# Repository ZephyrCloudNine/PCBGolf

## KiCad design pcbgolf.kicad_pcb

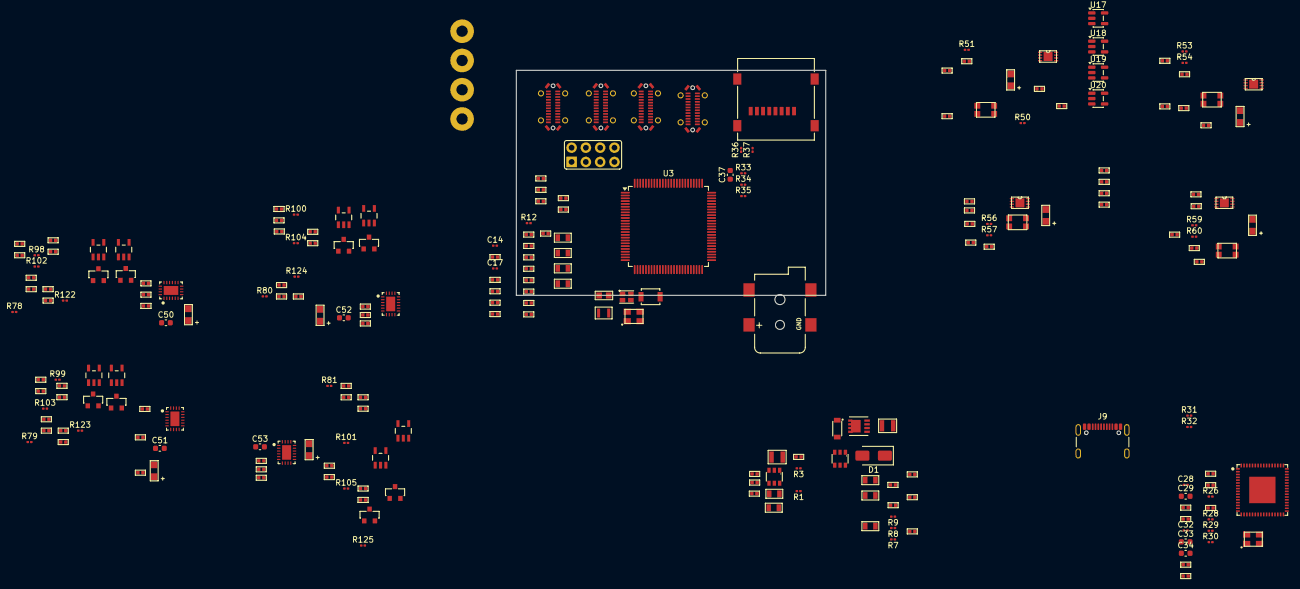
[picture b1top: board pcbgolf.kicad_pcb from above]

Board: 4 copper layers, 55.0 x 40.0 mm, 232 parts (0 on the bottom side), 184 nets, no tracks yet.

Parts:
BH1, BH2, BH3, BH4: M2_BOLT
C1, C3, C8, C12, C13, C15, C19, C20, C21: 10uF; 0805-C
C2, C4, C5, C7, C9, C11, C16, C18, C22, C23, C24, C26, C27, C30, C31, C35, C36, C38, C39, C40, C41, C42, C43, C44, C45, C46, C47, C48, C49: 100nF; 0402-C
C14, C17, C28, C32: 12pF; C_0201_0603Metric
C25: 220pF; 0402-C
C29, C33, C34, C37, C50, C51, C52, C53: 10uF; C_0603_1608Metric
D1: TVS-BI-DO214AA; D_SMA
D2: DIODEDB2W40100L; SOD-123F
J1: DCBARRELSMT; DCJACK_2MM_SMT
J2: MICRO_SD-0472192001; 0472192001
J4: CAN; 2X04
J5, J6, J7, J8: USB-C-FEMALEGCT; USB-C-FEMALE-VERT-GCT
J9: USB_C_Receptacle_USB2.0_16P; USB_C_Receptacle_GCT_USB4105-xx-A_16P_TopMnt_Horizontal
L1, L2: 3u3; L-1008
L3: L-US-L2; 0603-L
L4: 2u2; 0806
L5, L6, L7, L8: ACT1210D_CHOKE; CHOKE-3.2X2.5
LED1: CREE-RGB-CLMVC
LED2: CAN0; CHIPLED
LED3: CAN1; CHIPLED
LED4: CAN2; CHIPLED
LED5: CAN3; CHIPLED
LED6, LED7, LED8, LED9: CH1_PWR; CHIPLED
LED10, LED11, LED12, LED13, LED14, LED15, LED16, LED17: LED-CC-GREEN-RED-AM23ESG; SOT23-3
Q1: SIS427-VI; PP-1212-8
Q2, Q3, Q4, Q5, Q6, Q7, Q8, Q9: NFET-DUAL-COMMON-SOURCE-QS5K2; SOT23-5
R1, R3, R7, R8, R9, R12, R28, R29, R30, R33, R34, R35, R36, R37, R50, R51, R53, R54, R56, R57, R59, R60, R78, R79, R80, R81, R98, R99, R100, R101, R102, R103, R104, R105, R122, R123, R124, R125: 10k; R_0201_0603Metric
R2, R21, R23, R90, R92, R94, R96, R114, R116, R118, R120: 1k; 0402-R
R4: 33K3; 0402-R
R10: 52k3; 0402-R
R13, R14, R15, R16, R17, R18, R19, R20, R24, R25, R52, R55, R58, R61: 100k; 0402-R
R22, R62, R63, R64, R65: 2k7; 0402-R
R26: 1M; R_0201_0603Metric
R27: 12k; 0402-R
R31, R32: 5.1K; R_0201_0603Metric
R46, R47, R48, R49: 60; 0402-R
R66, R67, R68, R69: 28k; 0402-R
R70, R71, R72, R73: 33k; 0402-R
R74, R75, R76, R77: 3k3; 0402-R
R82, R83, R84, R85, R86, R87, R88, R89, R91, R93, R95, R97, R106, R107, R108, R109, R110, R111, R112, R113, R115, R117, R119, R121: 100; 0402-R
SW1: SW_SPST; SW_SPST_B3U-1000P
U1, U2: AP62300T; SOT23-6
U3: STM32H725ZGTx; LQFP-100_14x14mm_P0.5mm
U4: USB2517; QFN64-9X9
U5, U6, U7, U8: MCP2542FDT-E/MNY; TDFN8_2X3MC_MCH
U13, U14, U15, U16: TPS25942; WQFN20
U17, U18, U19, U20: OPA197xDBV; SOT-23-5
Y1: 25MHz; XTAL-3.2X2.5
Y2: 24MHz; XTAL-3.2X2.5

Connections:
+3V3: C7.1, C8.1, C19.1, C20.1, C23.1, C24.1, C26.1, C27.1, C30.2, C31.2, C37.1, C42.1, C43.1, C44.1, C45.1, J2.4 (VDD), L1.2, L3.1, LED1.U1 (COM+), R4.1, R28.1, R29.1, R30.1, R33.1, R34.1, R35.1, R36.1, R37.1, SW1.2 (B), U3.4 (VDD), U3.5 (VBAT), U3.11 (VDDSMPS), U3.20 (VDD), U3.30 (VDD), U3.47 (VDD), U3.59 (VDD), U3.75 (VDD), U3.76 (VDD33USB), U3.88 (VDD), U3.100 (VDD), U4.5 (VDDA33), U4.10 (VDDA33), U4.13 (CFG_SEL2), U4.24 (VDD33CR), U4.42 (CFG_SEL1), U4.43 (RESET_N), U4.46 (VDD33), U4.52 (VDDA33), U4.57 (VDDA33), U4.64 (VDD33PLL), U5.5 (VIO), U6.5 (VIO), U7.5 (VIO), U8.5 (VIO)
+5V: C1.1, C2.1, C11.1, C12.1, C13.1, C38.1, C39.1, C40.1, C41.1, L2.2, R1.1, R10.2, R52.2, R55.2, R58.2, R61.2, U1.3 (IN), U5.3 (VDD), U6.3 (VDD), U7.3 (VDD), U8.3 (VDD)
+12V: C3.1, C5.1, C46.1, C47.1, C48.1, C49.1, C50.1, C51.1, C52.1, C53.1, D2.1 (C), Q1.1 (S), Q1.2 (S), Q1.3 (S), R7.1, U2.3 (IN), U13.9 (VIN), U13.10 (VIN), U13.11 (VIN), U13.12 (VIN), U13.13 (VIN), U14.9 (VIN), U14.10 (VIN), U14.11 (VIN), U14.12 (VIN), U14.13 (VIN), U15.9 (VIN), U15.10 (VIN), U15.11 (VIN), U15.12 (VIN), U15.13 (VIN), U16.9 (VIN), U16.10 (VIN), U16.11 (VIN), U16.12 (VIN), U16.13 (VIN), U17.5 (V+), U18.5 (V+), U19.5 (V+), U20.5 (V+)
BTN: R12.2, SW1.1 (A), U3.8 (PC15), U3.94 (BOOT0)
CAN0_EN: U3.93 (PB7), U5.8 (STBY)
CAN0_H: J4.2, J5.A2 (TX1+), J6.A2 (TX1+), J7.A2 (TX1+), J8.A2 (TX1+), L5.4, R46.2, R50.1
CAN0_L: J4.1, J5.A3 (TX1-), J6.A3 (TX1-), J7.A3 (TX1-), J8.A3 (TX1-), L5.3, R46.1, R51.1
CAN0_RX: U3.95 (PB8), U5.4 (RXD)
CAN0_TX: U3.96 (PB9), U5.1 (TXD)
CAN1_EN: U3.89 (PB3(JTDO), U6.8 (STBY)
CAN1_H: J4.4, J5.A11 (RX2+), J6.A11 (RX2+), J7.A11 (RX2+), J8.A11 (RX2+), L6.4, R47.2, R53.1
CAN1_L: J4.3, J5.A10 (RX2-), J6.A10 (RX2-), J7.A10 (RX2-), J8.A10 (RX2-), L6.3, R47.1, R54.1
CAN1_RX: U3.91 (PB5), U6.4 (RXD)
CAN1_TX: U3.92 (PB6), U6.1 (TXD)
CAN2_EN: U3.53 (PD9), U7.8 (STBY)
CAN2_H: J4.6, J5.B2 (TX2+), J6.B2 (TX2+), J7.B2 (TX2+), J8.B2 (TX2+), L7.4, R48.2, R56.1
CAN2_L: J4.5, J5.B3 (TX2-), J6.B3 (TX2-), J7.B3 (TX2-), J8.B3 (TX2-), L7.3, R48.1, R57.1
CAN2_RX: U3.56 (PD12), U7.4 (RXD)
CAN2_TX: U3.57 (PD13), U7.1 (TXD)
CAN3_EN: U3.90 (PB4(NJTRST)), U8.8 (STBY)
CAN3_H: J4.8, J5.B11 (RX1+), J6.B11 (RX1+), J7.B11 (RX1+), J8.B11 (RX1+), L8.4, R49.2, R59.1
CAN3_L: J4.7, J5.B10 (RX1-), J6.B10 (RX1-), J7.B10 (RX1-), J8.B10 (RX1-), L8.3, R49.1, R60.1
CAN3_RX: U3.48 (PB12), U8.4 (RXD)
CAN3_TX: U3.49 (PB13), U8.1 (TXD)
CH1_D_N: J5.A7 (D-A), J5.B7 (D-B), U4.1 (USBDN1_DM)
CH1_D_P: J5.A6 (D+A), J5.B6 (D+B), U4.2 (USBDN1_DP)
CH1_IMON: R70.2, U3.34 (PA7), U13.19 (IMON)
CH1_PWR_EN: U3.25 (PA0), U13.14 (EN)
CH1_SBU1: J5.A8 (SBU1), R19.2, R90.2, R91.2
CH1_SBU1_IGN: Q2.1 (G1), R78.1, R83.2, U3.82 (PD0)
CH1_SBU1_RELAY: Q2.3 (G2), R82.2, R98.2, U3.83 (PD1)
CH1_SBU2: J5.B8 (SBU2), R20.2, R114.2, R115.2
CH1_SBU2_IGN: Q6.1 (G1), R102.1, R107.2, U3.85 (PD3)
CH1_SBU2_RELAY: Q6.3 (G2), R106.2, R122.2, U3.86 (PD4)
CH2_D_N: J6.A7 (D-A), J6.B7 (D-B), U4.3 (USBDN2_DM)
CH2_D_P: J6.A6 (D+A), J6.B6 (D+B), U4.4 (USBDN2_DP)
CH2_IMON: R71.2, U3.33 (PA6), U14.19 (IMON)
CH2_PWR_EN: U3.26 (PA1), U14.14 (EN)
CH2_SBU1: J6.A8 (SBU1), R15.2, R92.2, R93.2
CH2_SBU1_IGN: Q3.1 (G1), R79.1, R85.2, U3.87 (PD5)
CH2_SBU1_RELAY: Q3.3 (G2), R84.2, R99.2, U3.52 (PD8)
CH2_SBU2: J6.B8 (SBU2), R13.2, R116.2, R117.2
CH2_SBU2_IGN: Q7.1 (G1), R103.1, R109.2, U3.54 (PD10)
CH2_SBU2_RELAY: Q7.3 (G2), R108.2, R123.2, U3.60 (PD14)
CH3_D_N: J7.A7 (D-A), J7.B7 (D-B), U4.6 (USBDN3_DM)
CH3_D_P: J7.A6 (D+A), J7.B6 (D+B), U4.7 (USBDN3_DP)
CH3_IMON: R72.2, U3.32 (PA5), U15.19 (IMON)
CH3_PWR_EN: U3.27 (PA2), U15.14 (EN)
CH3_SBU1: J7.A8 (SBU1), R17.2, R94.2, R95.2
CH3_SBU1_IGN: Q4.1 (G1), R80.1, R87.2, U3.66 (PA8)
CH3_SBU1_RELAY: Q4.3 (G2), R86.2, R100.2, U3.61 (PD15)
CH3_SBU2: J7.B8 (SBU2), R18.2, R118.2, R119.2
CH3_SBU2_IGN: Q8.1 (G1), R104.1, R111.2, U3.55 (PD11)
CH3_SBU2_RELAY: Q8.3 (G2), R110.2, R124.2, U3.67 (PA9)
CH4_D_N: J8.A7 (D-A), J8.B7 (D-B), U4.8 (USBDN4_DM)
CH4_D_P: J8.A6 (D+A), J8.B6 (D+B), U4.9 (USBDN4_DP)
CH4_IMON: R73.2, U3.31 (PA4), U16.19 (IMON)
CH4_PWR_EN: U3.28 (PA3), U16.14 (EN)
CH4_SBU1: J8.A8 (SBU1), R16.2, R96.2, R97.2
CH4_SBU1_IGN: Q5.1 (G1), R81.1, R89.2, U3.38 (PB1)
CH4_SBU1_RELAY: Q5.3 (G2), R88.2, R101.2, U3.39 (PB2)
CH4_SBU2: J8.B8 (SBU2), R14.2, R120.2, R121.2
CH4_SBU2_IGN: Q9.1 (G1), R105.1, R113.2, U3.1 (PE2)
CH4_SBU2_RELAY: Q9.3 (G2), R112.2, R125.2, U3.2 (PE4)
GND: BH1.0 (1_0), BH2.0 (1_0), BH3.0 (1_0), BH4.0 (1_0), C1.2, C2.2, C3.2, C5.2, C7.2, C8.2, C11.2, C12.2, C13.2, C14.2, C15.2, C16.2, C17.2, C18.2, C19.2, C20.2, C21.2, C22.2, C23.2, C24.2, C25.2, C26.2, C27.2, C28.2, C29.2, C30.1, C31.1, C32.2, C33.2, C34.2, C35.1, C36.1, C37.2, C38.2, C39.2, C40.2, C41.2, C42.2, C43.2, C44.2, C45.2, C46.2, C47.2, C48.2, C49.2, C50.2, C51.2, C52.2, C53.2, D1.1, J1.GND (GNDBREAK), J1.GNDBREAK (GND), J2.6 (VSS), J2.G1 (GND), J2.G2 (GND), J2.G3 (GND), J2.G4 (GND), J5.A1 (GND), J5.A12 (GND), J5.B1 (GND), J5.B12 (GND), J5.S1 (SHIELDA), J5.S2 (SHIELDA), J5.S3 (SHIELDA), J5.S4 (SHIELDA), J5.S11 (SHIELDB), J5.S12 (SHIELDB), J5.S13 (SHIELDB), J5.S14 (SHIELDB), J6.A1 (GND), J6.A12 (GND), J6.B1 (GND), J6.B12 (GND), J6.S1 (SHIELDA), J6.S2 (SHIELDA), J6.S3 (SHIELDA), J6.S4 (SHIELDA), J6.S11 (SHIELDB), J6.S12 (SHIELDB), J6.S13 (SHIELDB), J6.S14 (SHIELDB), J7.A1 (GND), J7.A12 (GND), J7.B1 (GND), J7.B12 (GND), J7.S1 (SHIELDA), J7.S2 (SHIELDA), J7.S3 (SHIELDA), J7.S4 (SHIELDA), J7.S11 (SHIELDB), J7.S12 (SHIELDB), J7.S13 (SHIELDB), J7.S14 (SHIELDB), J8.A1 (GND), J8.A12 (GND), J8.B1 (GND), J8.B12 (GND), J8.S1 (SHIELDA), J8.S2 (SHIELDA), J8.S3 (SHIELDA), J8.S4 (SHIELDA), J8.S11 (SHIELDB), J8.S12 (SHIELDB), J8.S13 (SHIELDB), J8.S14 (SHIELDB), J9.A1 (GND), J9.A12 (GND), J9.B1 (GND), J9.B12 (GND), J9.SH (SHIELD), LED2.C, LED3.C, LED4.C, LED5.C, LED6.C, LED7.C, LED8.C, LED9.C, LED10.3 (C), LED11.3 (C), LED12.3 (C), LED13.3 (C), LED14.3 (C), LED15.3 (C), LED16.3 (C), LED17.3 (C), Q2.2 (S), Q3.2 (S), Q4.2 (S), Q5.2 (S), Q6.2 (S), Q7.2 (S), Q8.2 (S), Q9.2 (S), R2.1, R3.2, R8.2, R9.2, R12.1, R25.1, R27.1, R31.2, R32.2, R66.1, R67.1, R68.1, R69.1, R70.1, R71.1, R72.1, R73.1, R78.2, R79.2, R80.2, R81.2, R98.1, R99.1, R100.1, R101.1, R102.2, R103.2, R104.2, R105.2, R122.1, R123.1, R124.1, R125.1, U1.1 (GND), U2.1 (GND), U3.9 (VSSSMPS), U3.21 (VSS), U3.22 (VSSA), U3.29 (VSS), U3.45 (VSS), U3.58 (VSS), U3.73 (VSS), U3.98 (VSS), U4.19 (TEST), U4.PAD (VSS), U5.2 (VSS), U5.PAD (EPAD), U6.2 (VSS), U6.PAD (EPAD), U7.2 (VSS), U7.PAD (EPAD), U8.2 (VSS), U8.PAD (EPAD), U13.3 (PGTH), U13.15 (OVP), U13.16 (GND), U13.PAD (GND), U14.3 (PGTH), U14.15 (OVP), U14.16 (GND), U14.PAD (GND), U15.3 (PGTH), U15.15 (OVP), U15.16 (GND), U15.PAD (GND), U16.3 (PGTH), U16.15 (OVP), U16.16 (GND), U16.PAD (GND), U17.2 (V-), U18.2 (V-), U19.2 (V-), U20.2 (V-), Y1.2 (3), Y1.4 (3), Y2.2 (3), Y2.4 (3)
HUB_SCL: R30.2, U3.42 (PB10), U4.41 (SCL)
HUB_SDA: R28.2, U3.43 (PB11), U4.40 (SDA)
LED_B: R23.2, U3.3 (PE5)
LED_G: R22.2, U3.40 (PE7)
LED_R: R21.2, U3.41 (PE8)
unnamed: D2.2 (A), Q1.4 (G), R2.2
unnamed: D1.2, J1.PWR1 (PWR), Q1.5 (D), Q1.6 (D), Q1.7 (D), Q1.8 (D), Q1.9 (D)
unnamed: J5.A4 (VBUS), J5.A9 (VBUS), J5.B4 (VBUS), J5.B9 (VBUS), R74.1, U13.4 (VOUT), U13.5 (VOUT), U13.6 (VOUT), U13.7 (VOUT), U13.8 (VOUT)
unnamed: J6.A4 (VBUS), J6.A9 (VBUS), J6.B4 (VBUS), J6.B9 (VBUS), R75.1, U14.4 (VOUT), U14.5 (VOUT), U14.6 (VOUT), U14.7 (VOUT), U14.8 (VOUT)
unnamed: J7.A4 (VBUS), J7.A9 (VBUS), J7.B4 (VBUS), J7.B9 (VBUS), R76.1, U15.4 (VOUT), U15.5 (VOUT), U15.6 (VOUT), U15.7 (VOUT), U15.8 (VOUT)
unnamed: J8.A4 (VBUS), J8.A9 (VBUS), J8.B4 (VBUS), J8.B9 (VBUS), R77.1, U16.4 (VOUT), U16.5 (VOUT), U16.6 (VOUT), U16.7 (VOUT), U16.8 (VOUT)
unnamed: J9.A5 (CC1), R31.1
unnamed: J9.B5 (CC2), R32.1
unnamed: LED1.U4 (B-), R23.1
unnamed: LED1.U3 (G-), R22.1
unnamed: LED1.U2 (R-), R21.1
unnamed: LED2.A, R62.2
unnamed: LED3.A, R63.2
unnamed: LED4.A, R64.2
unnamed: LED5.A, R65.2
unnamed: LED6.A, R74.2
unnamed: LED7.A, R75.2
unnamed: LED8.A, R76.2
unnamed: LED9.A, R77.2
unnamed: LED10.2 (AG), R82.1
unnamed: LED10.1 (AR), R83.1
unnamed: LED11.2 (AG), R84.1
unnamed: LED11.1 (AR), R85.1
unnamed: LED12.2 (AG), R86.1
unnamed: LED12.1 (AR), R87.1
unnamed: LED13.2 (AG), R88.1
unnamed: LED13.1 (AR), R89.1
unnamed: LED14.2 (AG), R106.1
unnamed: LED14.1 (AR), R107.1
unnamed: LED15.2 (AG), R108.1
unnamed: LED15.1 (AR), R109.1
unnamed: LED16.2 (AG), R110.1
unnamed: LED16.1 (AR), R111.1
unnamed: LED17.2 (AG), R112.1
unnamed: LED17.1 (AR), R113.1
unnamed: Q2.5 (D1), R90.1
unnamed: Q2.4 (D2), R91.1
unnamed: Q3.5 (D1), R92.1
unnamed: Q3.4 (D2), R93.1
unnamed: Q4.5 (D1), R94.1
unnamed: Q4.4 (D2), R95.1
unnamed: Q5.5 (D1), R96.1
unnamed: Q5.4 (D2), R97.1
unnamed: Q6.5 (D1), R114.1
unnamed: Q6.4 (D2), R115.1
unnamed: Q7.5 (D1), R116.1
unnamed: Q7.4 (D2), R117.1
unnamed: Q8.5 (D1), R118.1
unnamed: Q8.4 (D2), R119.1
unnamed: Q9.5 (D1), R120.1
unnamed: Q9.4 (D2), R121.1
unnamed: R62.1, U17.1
unnamed: R63.1, U18.1
unnamed: R64.1, U19.1
unnamed: R65.1, U20.1
unnamed: C4.1, U1.6 (BST)
unnamed: R1.2, U1.5 (EN)
unnamed: R3.1, R4.2, U1.4 (FB)
unnamed: C4.2, L1.1, U1.2 (SW)
unnamed: C9.1, U2.6 (BST)
unnamed: R7.2, R8.1, U2.5 (EN)
unnamed: R9.1, R10.1, U2.4 (FB)
unnamed: C9.2, L2.1, U2.2 (SW)
unnamed: R17.1, U3.16 (PC0)
unnamed: R18.1, U3.17 (PC1)
unnamed: R19.1, U3.18 (PC2_C)
unnamed: R20.1, U3.19 (PC3_C)
unnamed: R13.1, U3.36 (PC5)
unnamed: R14.1, U3.62 (PC6)
unnamed: R15.1, U3.63 (PC7)
unnamed: R16.1, U3.7 (PC14)
unnamed: C14.1, U3.13 (PH0), Y1.1
unnamed: C17.1, U3.14 (PH1), Y1.3 (2)
unnamed: R27.2, U4.63 (RBIAS)
unnamed: R29.2, U4.45 (SUSP_IND)
unnamed: R24.1, R25.2, U4.44 (VBUS_DET)
unnamed: C33.1, C35.2, U4.25 (VDD18)
unnamed: C34.1, C36.2, U4.62 (VDD18PLL)
unnamed: C28.1, R26.2, U4.61 (XTAL1), Y2.1
unnamed: C32.1, R26.1, U4.60 (XTAL2), Y2.3 (2)
unnamed: L5.1, U5.7 (CANH)
unnamed: L5.2, U5.6 (CANL)
unnamed: L6.1, U6.7 (CANH)
unnamed: L6.2, U6.6 (CANL)
unnamed: L7.1, U7.7 (CANH)
unnamed: L7.2, U7.6 (CANL)
unnamed: L8.1, U8.7 (CANH)
unnamed: L8.2, U8.6 (CANL)
unnamed: R66.2, U13.17 (ILIM)
unnamed: R67.2, U14.17 (ILIM)
unnamed: R68.2, U15.17 (ILIM)
unnamed: R69.2, U16.17 (ILIM)
unnamed: R50.2, U17.3 (+)
unnamed: R51.2, R52.1, U17.4 (-)
unnamed: R53.2, U18.3 (+)
unnamed: R54.2, R55.1, U18.4 (-)
unnamed: R56.2, U19.3 (+)
unnamed: R57.2, R58.1, U19.4 (-)
unnamed: R59.2, U20.3 (+)
unnamed: R60.2, R61.1, U20.4 (-)
SD_CLK: J2.5 (CLK), U3.81 (PC12)
SD_CMD: J2.3 (CMD), R37.2, U3.84 (PD2)
SD_D0: J2.7 (DAT0), R33.2, U3.64 (PC8)
SD_D1: J2.8 (DAT1), R34.2, U3.65 (PC9)
SD_D2: J2.1 (DAT2), R35.2, U3.79 (PC10)
SD_D3: J2.2 (CD/DAT3), R36.2, U3.80 (PC11)
STM_D_N: U3.69 (PA11), U4.55 (USBDN7_DM)
STM_D_P: U3.70 (PA12), U4.56 (USBDN7_DP)
USB_D_N: J9.A7 (D-), J9.B7 (D-), U4.58 (USBUP_DM)
USB_D_P: J9.A6 (D+), J9.B6 (D+), U4.59 (USBUP_DP)
VBUS: C29.1, J9.A4 (VBUS), J9.A9 (VBUS), J9.B4 (VBUS), J9.B9 (VBUS), R24.2
VDDA: C22.1, L3.2, U3.23 (VREF+), U3.24 (VDDA)
VDDLDO: C15.1, C16.1, C18.1, C21.1, L4.1, U3.12 (VFBSMPS), U3.44 (VCAP), U3.46 (VDDLDO), U3.72 (VCAP), U3.74 (VDDLDO), U3.97 (VCAP), U3.99 (VDDLDO)
VLXSMPS: C25.1, L4.2, U3.10 (VLXSMPS)
